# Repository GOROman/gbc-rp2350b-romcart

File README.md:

# RP2350B ROM カートリッジ — R0設計試作

**設計レビュー用です。実機動作未確認、製造リリース未承認。発注しないでください。**

WaveShare Core2350B2-Kit（RP2350B、16MiB Flash、8MiB PSRAM）のキャリアを KiCad 10 で設計するローカル試作です。公開元のモジュール使用構想を参考にし、5V入力直結・5Vプルアップだけの案をそのまま採用せず、電圧変換と出力遮断を追加しました。

32KiB / MBCなし / SRAMなしは **初期検証範囲** であり、公開元で確定した仕様とは表現しません。Game Boy Color と ModRetro Chromatic の動作・ケース適合は未確認です。

- 回路図・配線完了した試作基板：`hardware/romcart.kicad_sch`, `.kicad_pcb`, `.kicad_pro`
- 型番付きBOM・検討用Gerber/Excellon・CPL：`manufacturing/`
- GPIO割当・64端子モジュール配置・一次資料：`docs/`
- PIOと安全停止を標準にしたファーム土台：`firmware/`
- ERC/DRCと製造出力検証結果：`validation/RESULTS.md`
- 公開用の実データ画像：`previews/`（スクリーン上の個人情報を含まないKiCad出力画像）

## 構成

M1は**手実装**。U1–U3は3.3V動作・5V入力許容のSN74LVC245A。U4はSN74LVC8T245による3.3V→本体5Vデータ出力。U5/U6が `/RD, A15, /WR, /RESET, VALID` を外部判定してHi-Zへ遮断します。Q1が起動時RESETを保持。D1はUSB側から本体への逆給電を遮断。各ICには100nF、各データ線には33Ωを配置しました。

3.3Vロジックを本体5V入力へ直接出す構成ではありません。RP2350の5V許容はFT GPIOかつ通電中に限るので、入力をバッファ経由にしています。

**標準ファームはVALID=0 / RESET保持**。実験PIOは応答が遅れると次サイクルへ古いデータが混入する問題を解決していません。動作するROMエミュレータが完成したとは表示しません。

## 製造と量産候補

キャリアは57.5×52.5mm、0.8mm、4層の試作外形。白 solder mask と接点のgold仕上げを想定。端子・シェル・面取り・モジュール高さは実物確認が必要です。Gerberを生成できることと製造/動作検証合格は別です。最新の未接続/DRC件数は検証結果をご覧ください。

低部品点数のSMD量産にはフラッシュ内蔵 **RP2354B** が有力です。親タスクでJLC実装在庫を確認しましたが、公式指定コア用インダクタが欠品。単体版の回路/基板/ガーバーはまだ作成していません。[比較と調達条件](docs/smd-cost-option.md)を参照してください。

## 再生成

`design.py` は配置を生成し **既存PCB配線を消す** ので、編集したPCBに対して無闇に再実行しないでください。`schematic.py` は部品仕様から回路図/シンボルを作成。`route.py` は実験的な配線補助であり、出力は必ずKiCad DRCで確認します。フットプリントはプロジェクトに同梱しています。

```sh
# macOSの既存KiCad付属Pythonを使用。新規依存の自動インストールなし。
KICAD_CONFIG_HOME="$PWD/.kicad-config" "/Applications/KiCad/KiCad.app/Contents/Frameworks/Python.framework/Versions/3.9/bin/python3" scripts/design.py
python3 scripts/schematic.py
```

ROM・認証情報・個人画面・購入情報は同梱していません。KiCad公式フットプリントのライセンスは `third_party/`。この試作がNintendo/Waveshare/ModRetroの認定品であるとの主張はありません。

## 回路図を見る

**ERC・DRC・ネット整合は合格。実機未検証・発注不可。** ピン割当と電圧変換回路を確認できる修正版です。画像だけを動作保証の証拠として扱わないでください。

## 基板を見る

**未接続0の配線修正版。実機未検証・発注不可。** ソフトウェア検証の合格と、基板端子・シェル・電源・バス応答の実機検証は区別しています。

修正後のネイティブPCBが正本です。初期配置generatorと修正スクリプトは作業履歴であり、PCBを再生成すると手直しした配線を失います。初回R0は `validation/r0-retained/` とGit履歴に保持しています。

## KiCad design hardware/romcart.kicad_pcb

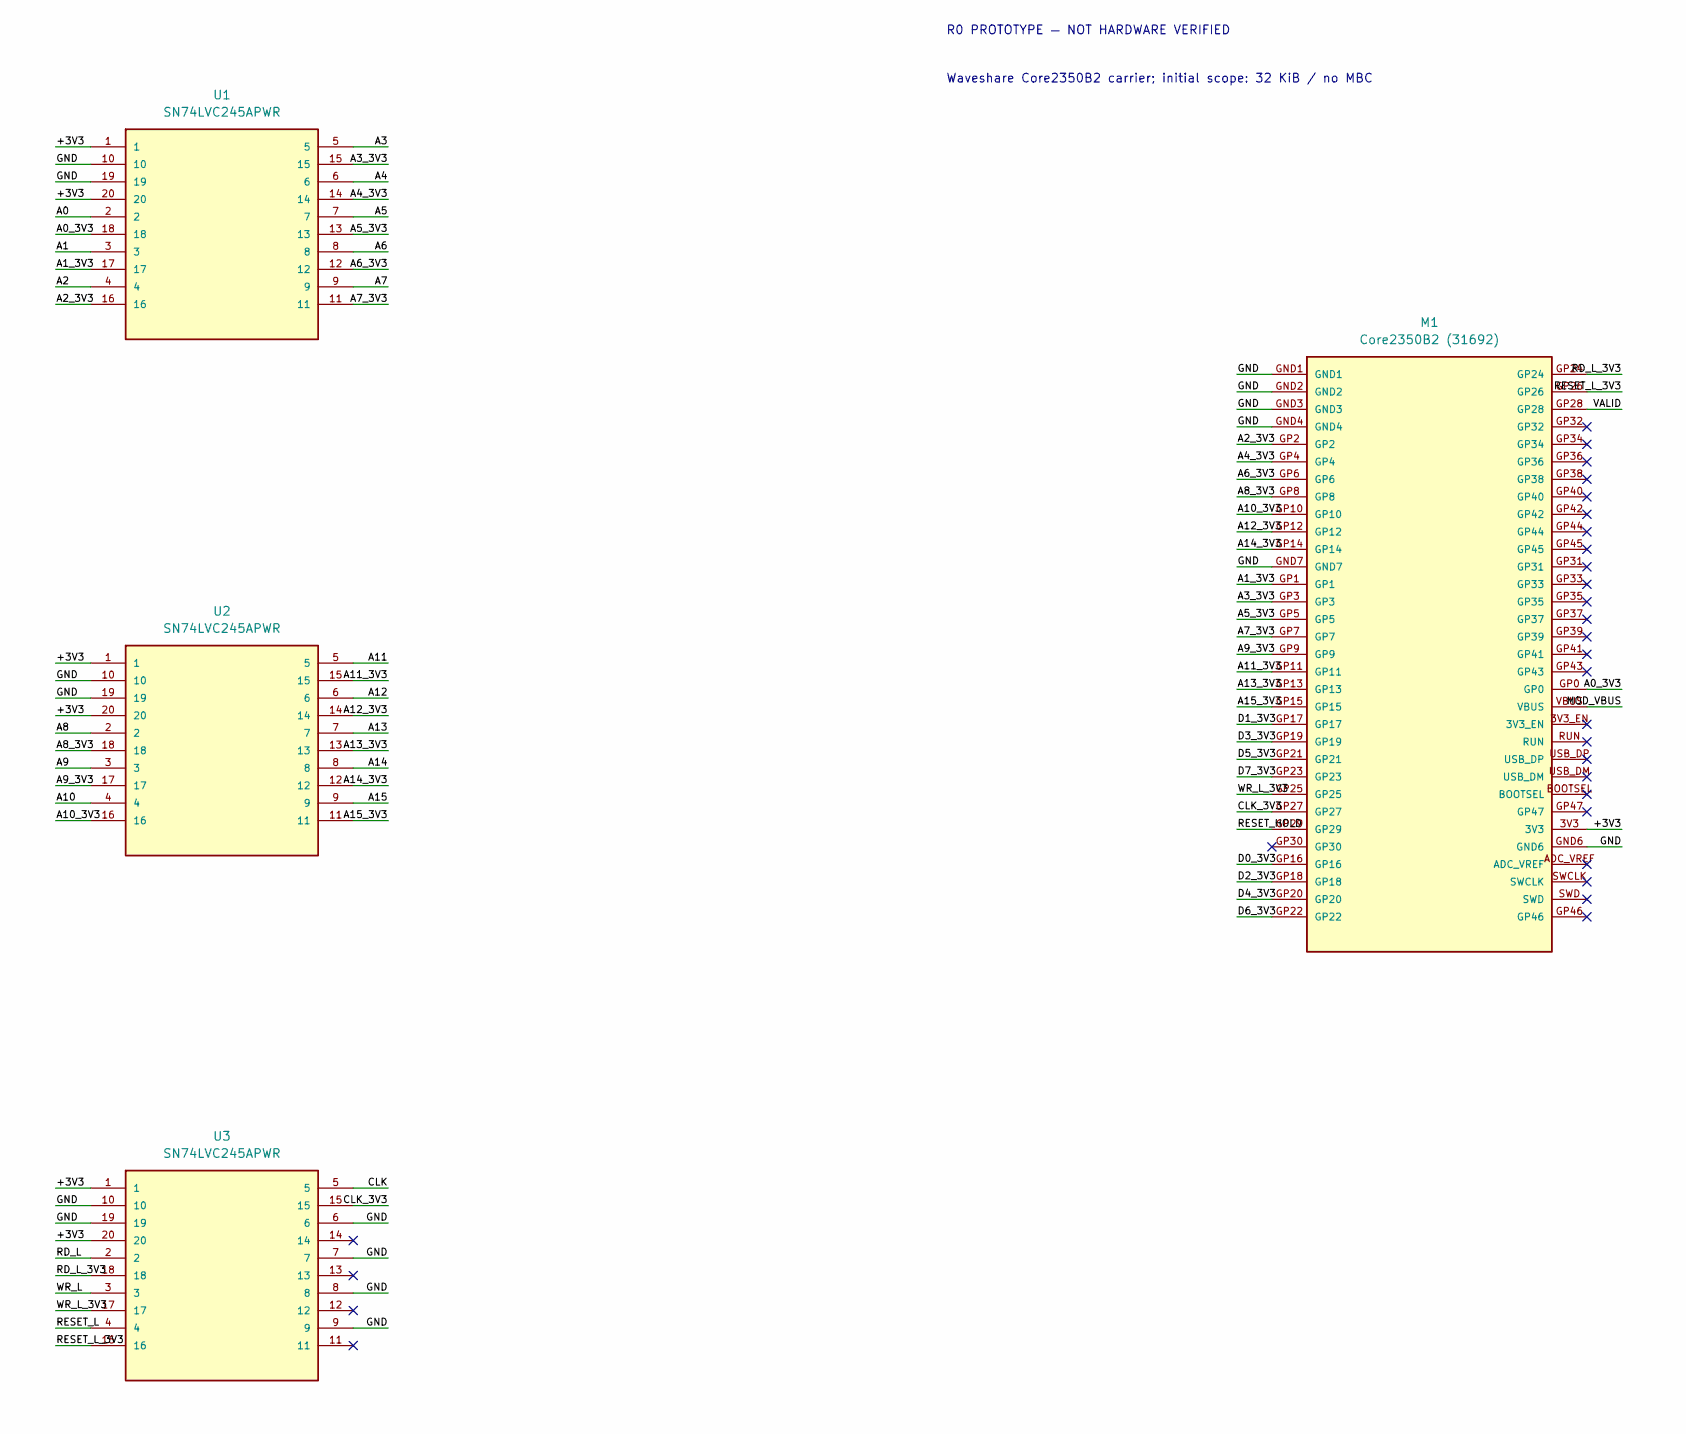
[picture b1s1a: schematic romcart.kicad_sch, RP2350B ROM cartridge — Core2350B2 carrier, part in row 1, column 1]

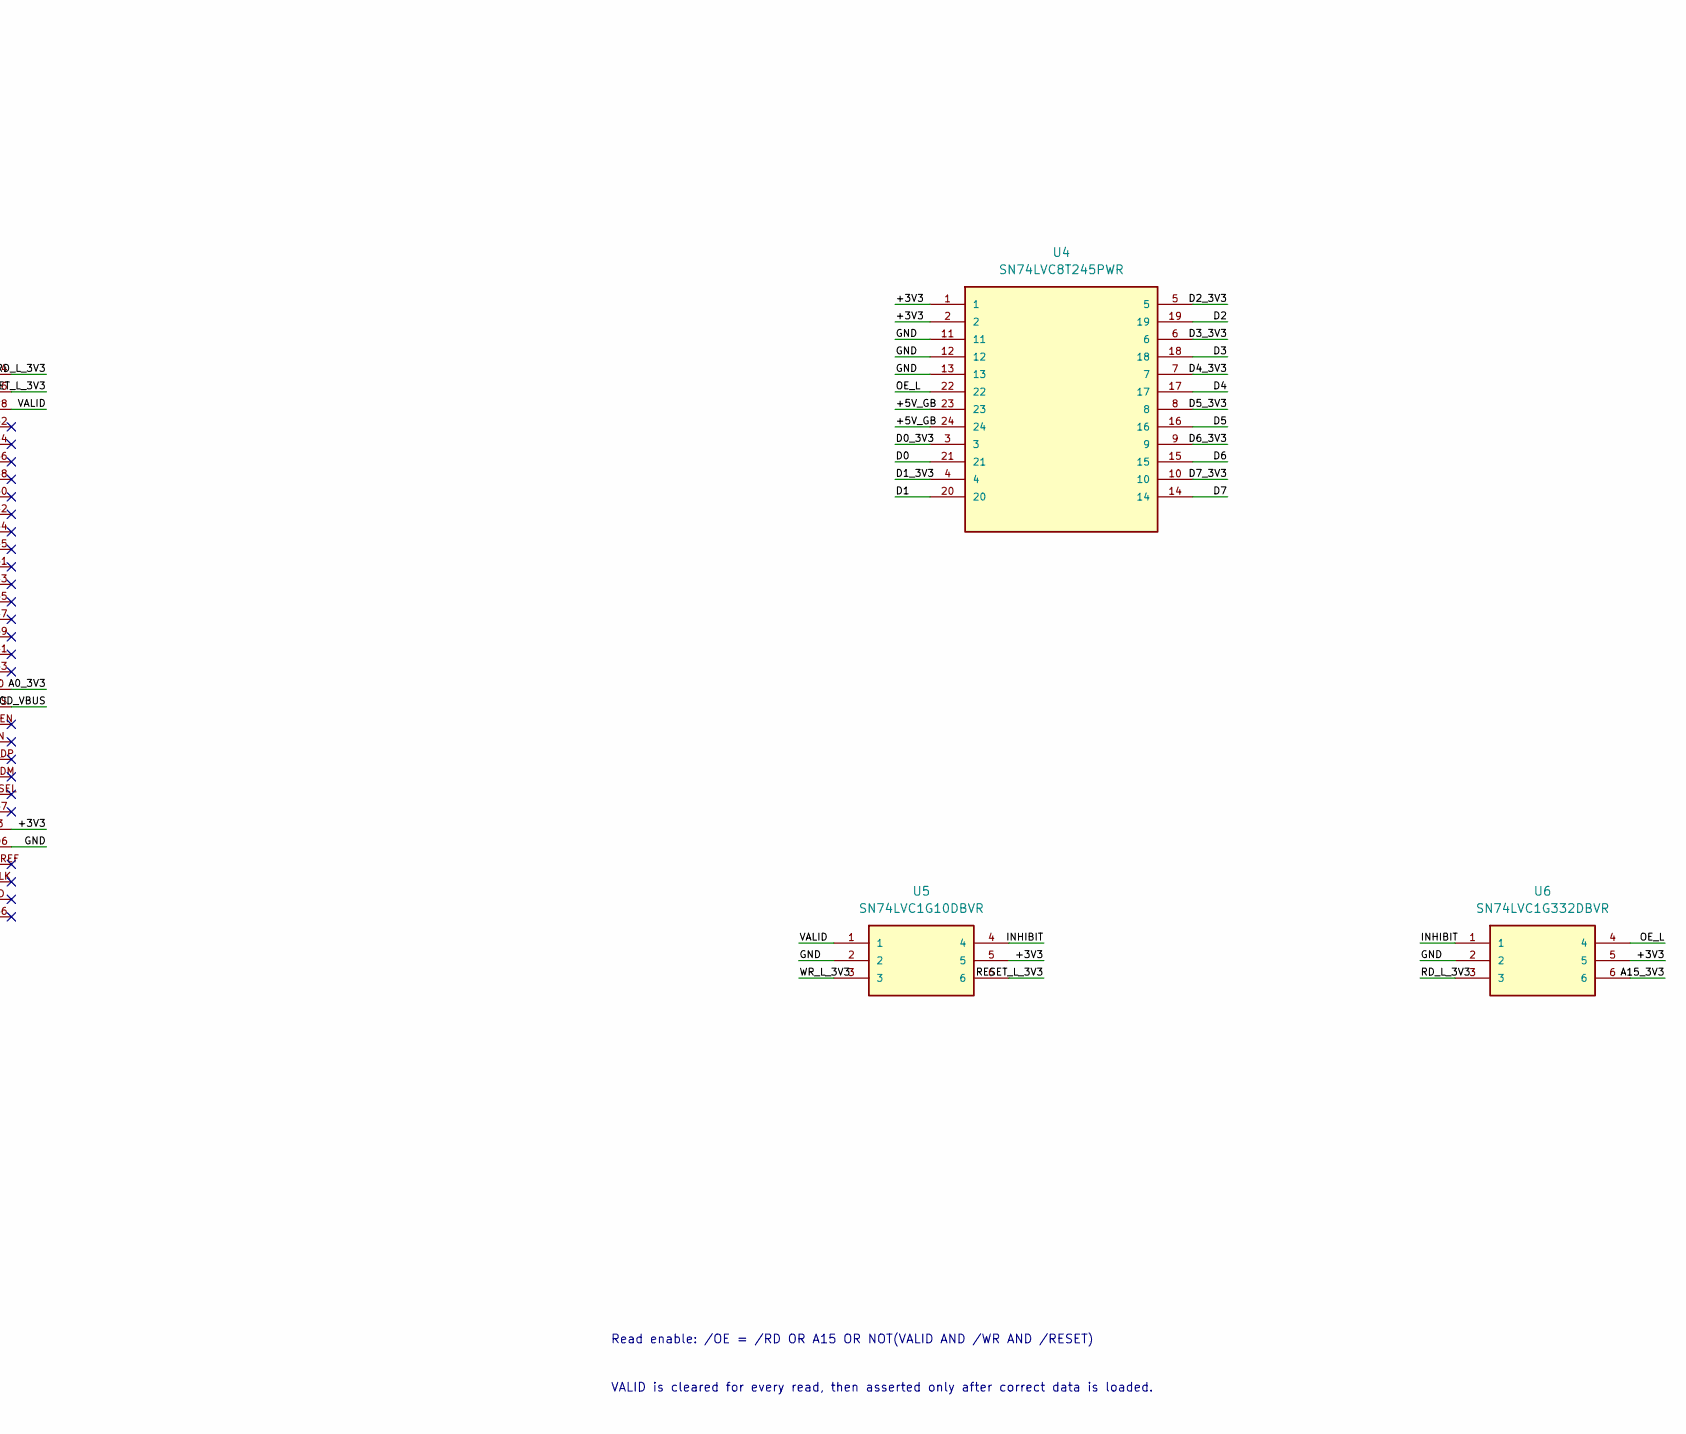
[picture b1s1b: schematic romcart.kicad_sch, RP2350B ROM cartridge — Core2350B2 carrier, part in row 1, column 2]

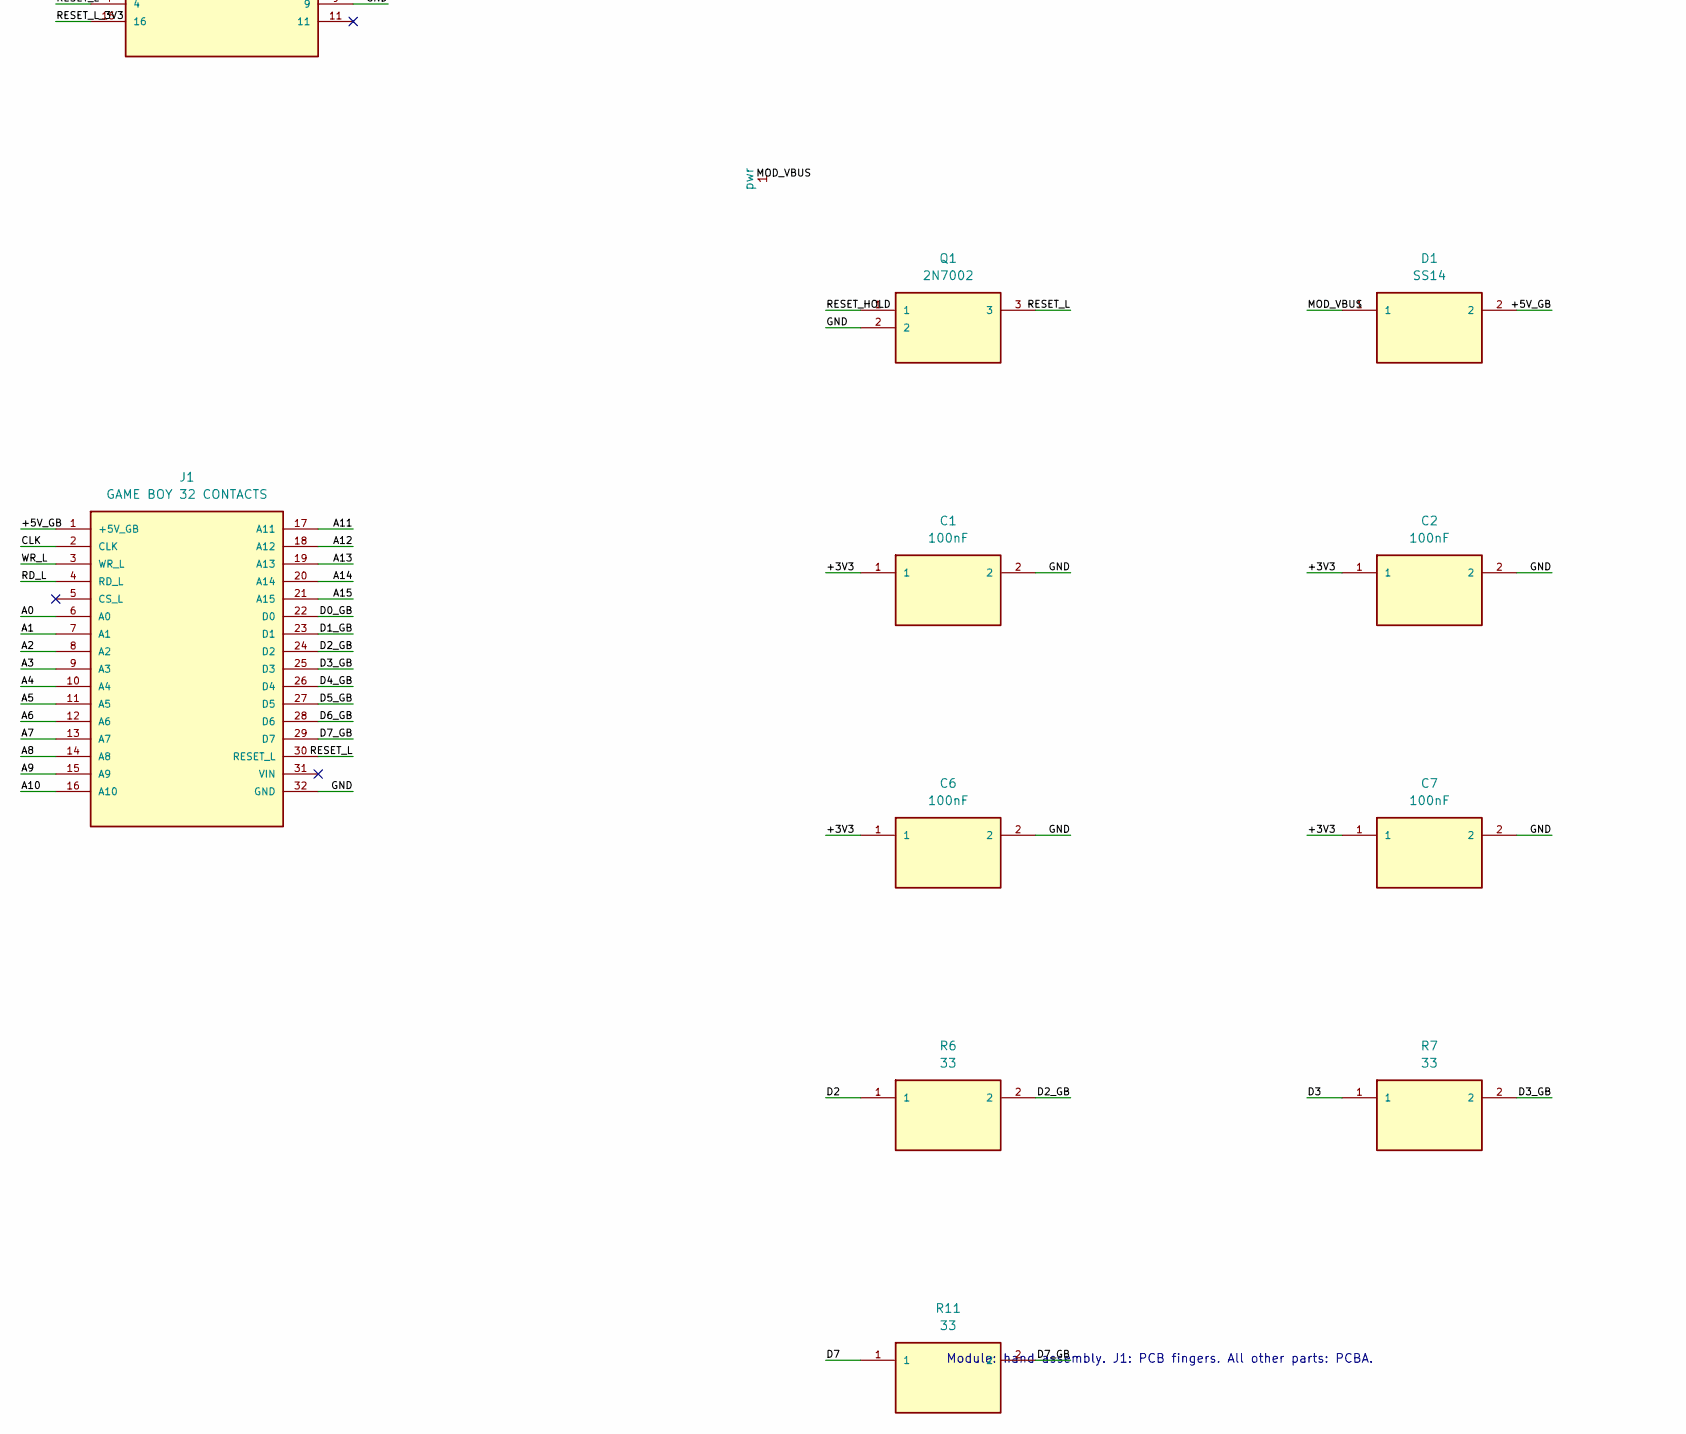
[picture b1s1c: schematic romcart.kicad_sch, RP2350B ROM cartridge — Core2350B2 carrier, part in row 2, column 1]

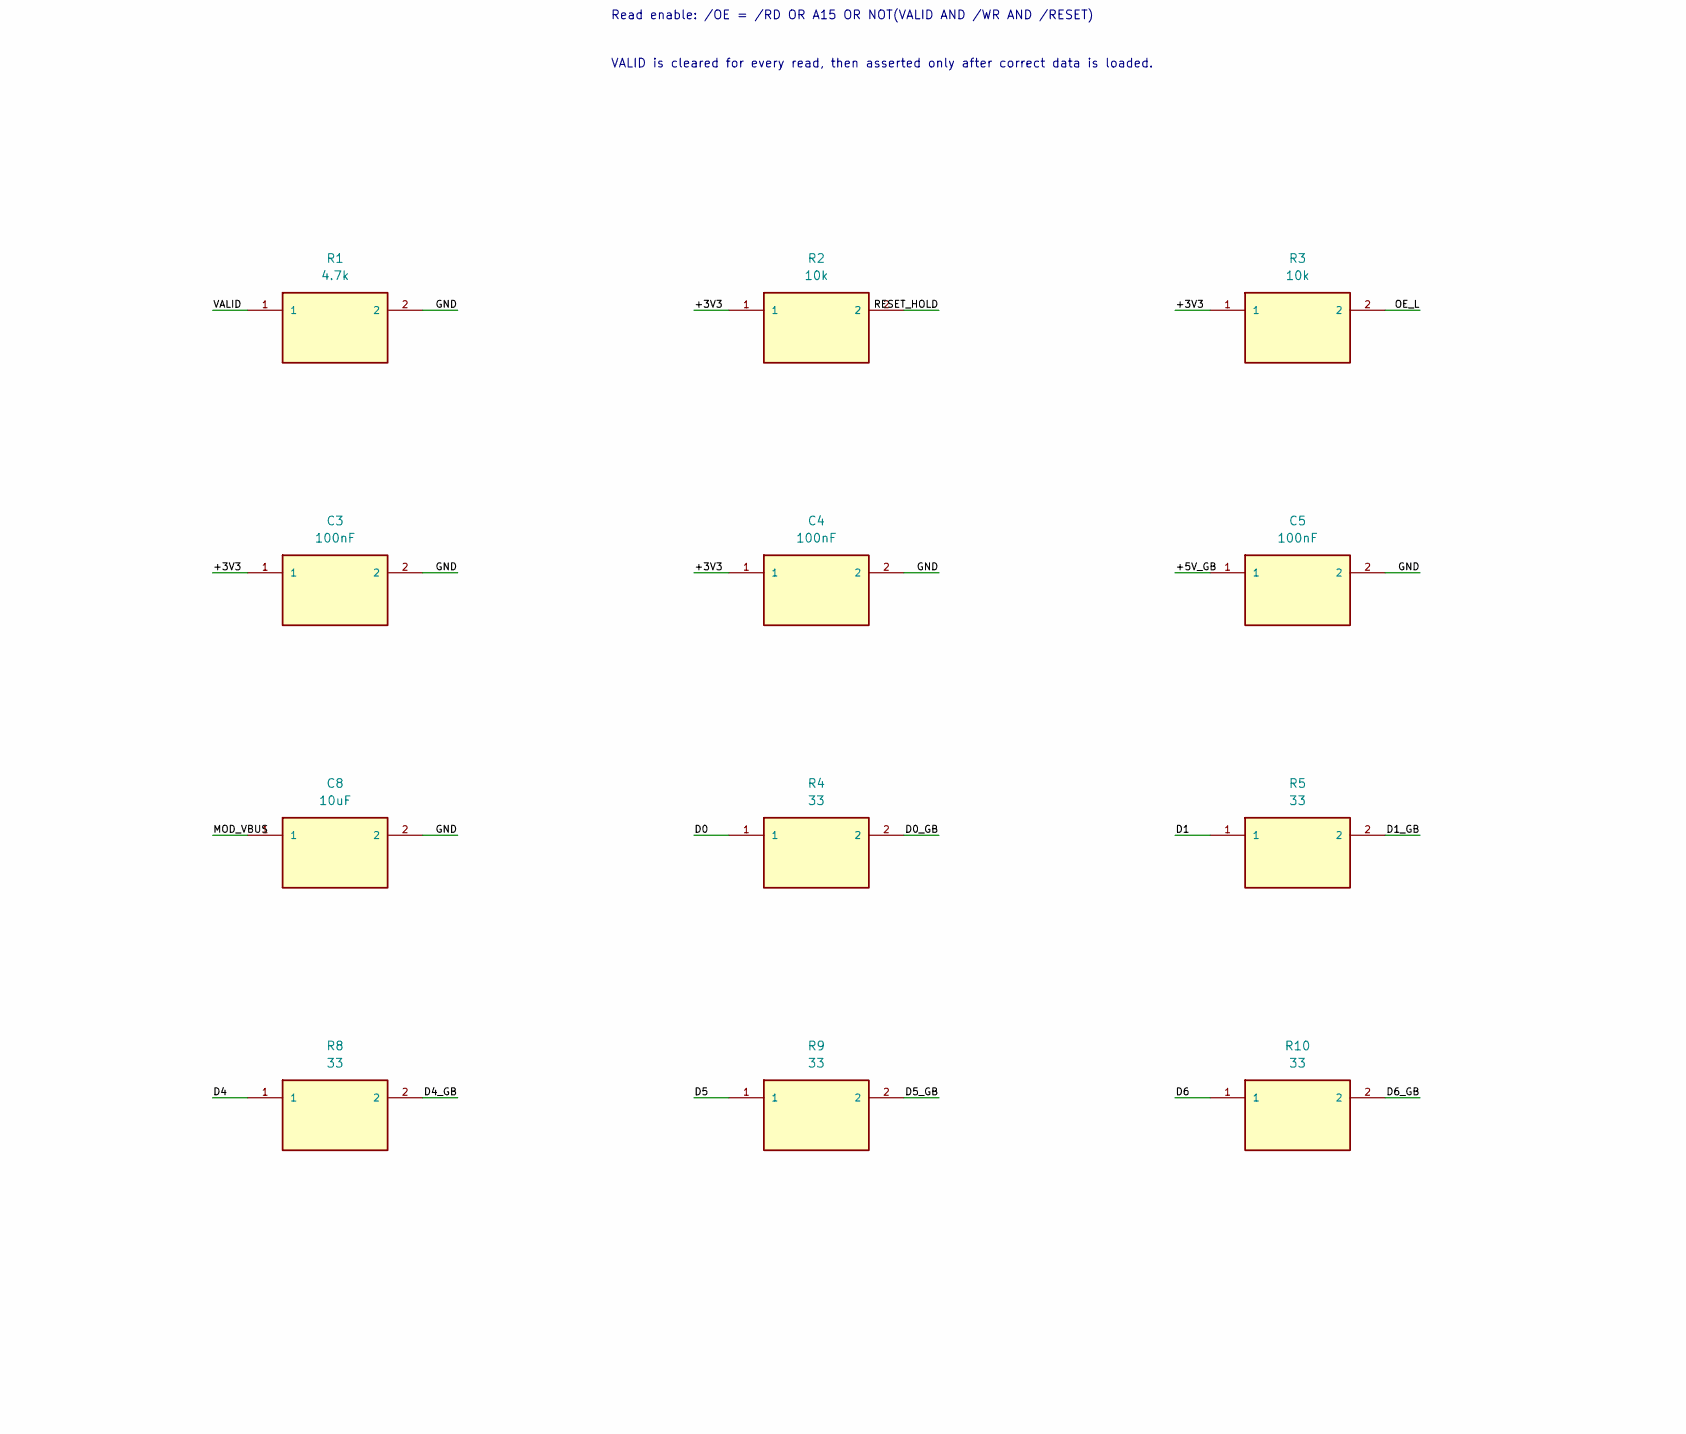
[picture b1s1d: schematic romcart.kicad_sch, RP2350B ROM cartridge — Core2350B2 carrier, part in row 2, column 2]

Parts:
C1, C2, C3, C4, C5, C6, C7: 100nF; C_0603_1608Metric; MPN GRM188R71H104KA93D
C8: 10uF; C_0805_2012Metric; MPN GRM21BR61A106KE19L
D1: SS14; D_SMA; MPN SS14
J1: GAME BOY 32 CONTACTS; GB_32_EDGE_1.50mm; MPN PCB gold fingers
M1: Core2350B2 (31692); Core2350B_64_TH; MPN Core2350B2-Kit
Q1: 2N7002; SOT-23; MPN 2N7002
R1: 4.7k; R_0603_1608Metric; MPN RC0603FR-074K7L
R2, R3: 10k; R_0603_1608Metric; MPN RC0603FR-0710KL
R4, R5, R6, R7, R8, R9, R10, R11: 33; R_0603_1608Metric; MPN RC0603FR-0733RL
U1, U2, U3: SN74LVC245APWR; TSSOP-20_4.4x6.5mm_P0.65mm; MPN SN74LVC245APWR
U4: SN74LVC8T245PWR; TSSOP-24_4.4x7.8mm_P0.65mm; MPN SN74LVC8T245PWR
U5: SN74LVC1G10DBVR; SOT-23-6; MPN SN74LVC1G10DBVR
U6: SN74LVC1G332DBVR; SOT-23-6; MPN SN74LVC1G332DBVR

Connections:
/+3V3: C1.1, C2.1, C3.1, C4.1, C6.1, C7.1, M1.3V3, R2.1, R3.1, U1.1, U1.20, U2.1, U2.20, U3.1, U3.20, U4.1, U4.2, U5.5, U6.5
/+5V_GB: C5.1, D1.2, J1.1 (+5V_GB), U4.23, U4.24
/A0: J1.6 (A0), U1.2
/A0_3V3: M1.GP0, U1.18
/A1: J1.7 (A1), U1.3
/A1_3V3: M1.GP1, U1.17
/A2: J1.8 (A2), U1.4
/A2_3V3: M1.GP2, U1.16
/A3: J1.9 (A3), U1.5
/A3_3V3: M1.GP3, U1.15
/A4: J1.10 (A4), U1.6
/A4_3V3: M1.GP4, U1.14
/A5: J1.11 (A5), U1.7
/A5_3V3: M1.GP5, U1.13
/A6: J1.12 (A6), U1.8
/A6_3V3: M1.GP6, U1.12
/A7: J1.13 (A7), U1.9
/A7_3V3: M1.GP7, U1.11
/A8: J1.14 (A8), U2.2
/A8_3V3: M1.GP8, U2.18
/A9: J1.15 (A9), U2.3
/A9_3V3: M1.GP9, U2.17
/A10: J1.16 (A10), U2.4
/A10_3V3: M1.GP10, U2.16
/A11: J1.17 (A11), U2.5
/A11_3V3: M1.GP11, U2.15
/A12: J1.18 (A12), U2.6
/A12_3V3: M1.GP12, U2.14
/A13: J1.19 (A13), U2.7
/A13_3V3: M1.GP13, U2.13
/A14: J1.20 (A14), U2.8
/A14_3V3: M1.GP14, U2.12
/A15: J1.21 (A15), U2.9
/A15_3V3: M1.GP15, U2.11, U6.6
/CLK: J1.2 (CLK), U3.5
/CLK_3V3: M1.GP27, U3.15
/D0: R4.1, U4.21
/D0_3V3: M1.GP16, U4.3
/D0_GB: J1.22 (D0), R4.2
/D1: R5.1, U4.20
/D1_3V3: M1.GP17, U4.4
/D1_GB: J1.23 (D1), R5.2
/D2: R6.1, U4.19
/D2_3V3: M1.GP18, U4.5
/D2_GB: J1.24 (D2), R6.2
/D3: R7.1, U4.18
/D3_3V3: M1.GP19, U4.6
/D3_GB: J1.25 (D3), R7.2
/D4: R8.1, U4.17
/D4_3V3: M1.GP20, U4.7
/D4_GB: J1.26 (D4), R8.2
/D5: R9.1, U4.16
/D5_3V3: M1.GP21, U4.8
/D5_GB: J1.27 (D5), R9.2
/D6: R10.1, U4.15
/D6_3V3: M1.GP22, U4.9
/D6_GB: J1.28 (D6), R10.2
/D7: R11.1, U4.14
/D7_3V3: M1.GP23, U4.10
/D7_GB: J1.29 (D7), R11.2
/GND: C1.2, C2.2, C3.2, C4.2, C5.2, C6.2, C7.2, C8.2, J1.32 (GND), M1.GND1, M1.GND2, M1.GND3, M1.GND4, M1.GND6, M1.GND7, Q1.2, R1.2, U1.10, U1.19, U2.10, U2.19, U3.6, U3.7, U3.8, U3.9, U3.10, U3.19, U4.11, U4.12, U4.13, U5.2, U6.2
/INHIBIT: U5.4, U6.1
/MOD_VBUS: C8.1, D1.1, M1.VBUS
/OE_L: R3.2, U4.22, U6.4
/RD_L: J1.4 (RD_L), U3.2
/RD_L_3V3: M1.GP24, U3.18, U6.3
/RESET_HOLD: M1.GP29, Q1.1, R2.2
/RESET_L: J1.30 (RESET_L), Q1.3, U3.4
/RESET_L_3V3: M1.GP26, U3.16, U5.6
/VALID: M1.GP28, R1.1, U5.1
/WR_L: J1.3 (WR_L), U3.3
/WR_L_3V3: M1.GP25, U3.17, U5.3

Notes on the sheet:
R0 PROTOTYPE — NOT HARDWARE VERIFIED
Waveshare Core2350B2 carrier; initial scope: 32 KiB / no MBC
Read enable: /OE = /RD OR A15 OR NOT(VALID AND /WR AND /RESET)
VALID is cleared for every read, then asserted only after correct data is loaded.
Module: hand assembly. J1: PCB fingers. All other parts: PCBA.

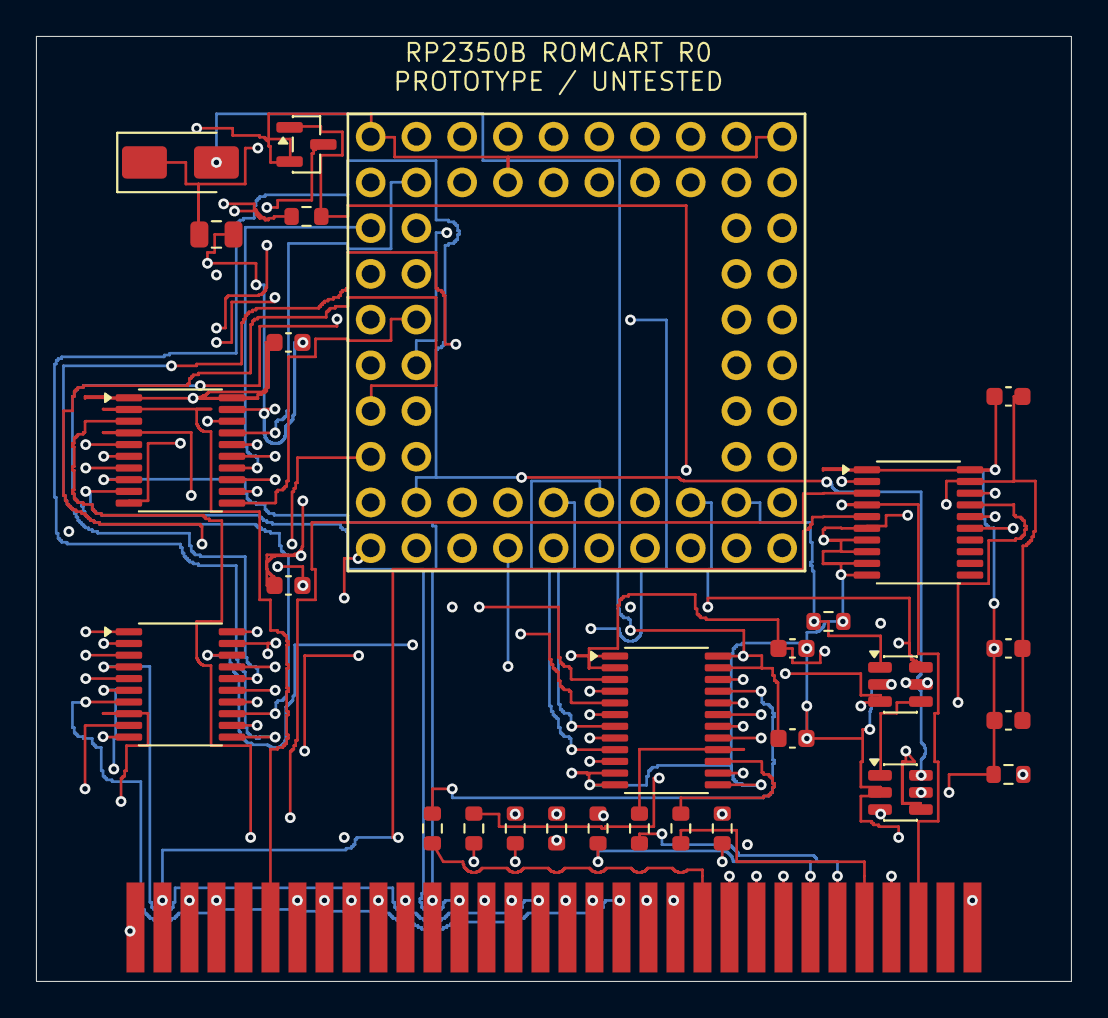
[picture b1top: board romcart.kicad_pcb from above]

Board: 4 copper layers, 57.5 x 52.5 mm, 29 parts (0 on the bottom side), 72 nets.

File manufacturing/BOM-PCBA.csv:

Comment,Designator,Footprint,Quantity,Manufacturer,MPN,LCSC Part #
SN74LVC245APWR,"U1,U2,U3",TSSOP-20_4.4x6.5mm_P0.65mm,3,Texas Instruments,SN74LVC245APWR,
SN74LVC8T245PWR,U4,TSSOP-24_4.4x7.8mm_P0.65mm,1,Texas Instruments,SN74LVC8T245PWR,
SN74LVC1G10DBVR,U5,SOT-23-6,1,Texas Instruments,SN74LVC1G10DBVR,
SN74LVC1G332DBVR,U6,SOT-23-6,1,Texas Instruments,SN74LVC1G332DBVR,
2N7002,Q1,SOT-23,1,Nexperia,2N7002,
SS14,D1,D_SMA,1,Diodes Incorporated,SS14,
4.7k,R1,R_0603_1608Metric,1,Yageo,RC0603FR-074K7L,
10k,"R2,R3",R_0603_1608Metric,2,Yageo,RC0603FR-0710KL,
100nF,"C1,C2,C3,C4,C5,C6,C7",C_0603_1608Metric,7,Murata,GRM188R71H104KA93D,
10uF,C8,C_0805_2012Metric,1,Murata,GRM21BR61A106KE19L,
33,"R4,R5,R6,R7,R8,R9,R10,R11",R_0603_1608Metric,8,Yageo,RC0603FR-0733RL,

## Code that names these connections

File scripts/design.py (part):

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 s=k.PCB_SHAPE(f);s.SetShape(k.SHAPE_T_SEGMENT);s.SetStart(mm(*a));s.SetEnd(mm(*c));s.SetWidth(round(width*1e6));s.SetLayer(layer);f.Add(s)
for a,c in [((-12.7,-12.7),(12.7,-12.7)),((12.7,-12.7),(12.7,12.7)),((12.7,12.7),(-12.7,12.7)),((-12.7,12.7),(-12.7,-12.7))]:line(f,a,c)
for a,c in [((-13,-13),(13,-13)),((13,-13),(13,13)),((13,13),(-13,13)),((-13,13),(-13,-13))]:line(f,a,c,k.F_CrtYd,.05)
pins={n:None for n in pos};pins.update({n:'GND' for n in pos if n.startswith('GND')});pins['VBUS']='MOD_VBUS';pins['3V3']='+3V3'
for i in range(16):pins['GP'+str(i)]='A'+str(i)+'_3V3'
for i in range(8):pins['GP'+str(16+i)]='D'+str(i)+'_3V3'
for i,n in enumerate(['RD_L','WR_L','RESET_L','CLK']):pins['GP'+str(24+i)]=n+'_3V3'
pins['GP28']='VALID';pins['GP29']='RESET_HOLD'
types={n:'input' for n in pins if n.startswith('GP')};types.update({n:'output' for n in ['GP'+str(i) for i in range(16,24)]+['GP28','GP29']});types.update(VBUS='power_in',**{'3V3':'power_out'});types.update({n:'passive' for n in pins if n.startswith('GND')})
add('M1','Core2350B2 (31692)',f,30,17,pins,'Core2350B2-Kit','Waveshare','HAND',types=types)
# 5V tolerant input, fixed direction A->B at 3.3 V. Ioff on power loss.
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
